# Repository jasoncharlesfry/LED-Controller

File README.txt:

This is a three channel analog LED dimmer. It operates at 15-60V and 1A per channel. It is based on the iw339 PWM controller IC. There is no current regulation so this board is only appropriate for LEDs with current-limiting resistors.

The pulse width of each channel is controlled by a 100k potentiometer. It is easier to control the brightness precisely with an audio taper pot. 

The board has positions for 4 switches. SW0 breaks VIN for all channels. SW1, SW2, and SW3 break VIN for channels 1, 2, and 3 respectively. All of the switches are optional and may be replaced with jumper wires depending on what is convenient for the application. 

The mosfet listed on the bom may not be in stock and can be replaced with any TO-252 mosfet with appropriate specifications (the threshold should be below 5V, Vgs-max should be above 15V, Vds-max should be above VIN, and Id-max should be above the current drawn by the LEDs).

Do not replace the fuse with a jumper. Use an appropriately sized 2AG fast-blow fuse.

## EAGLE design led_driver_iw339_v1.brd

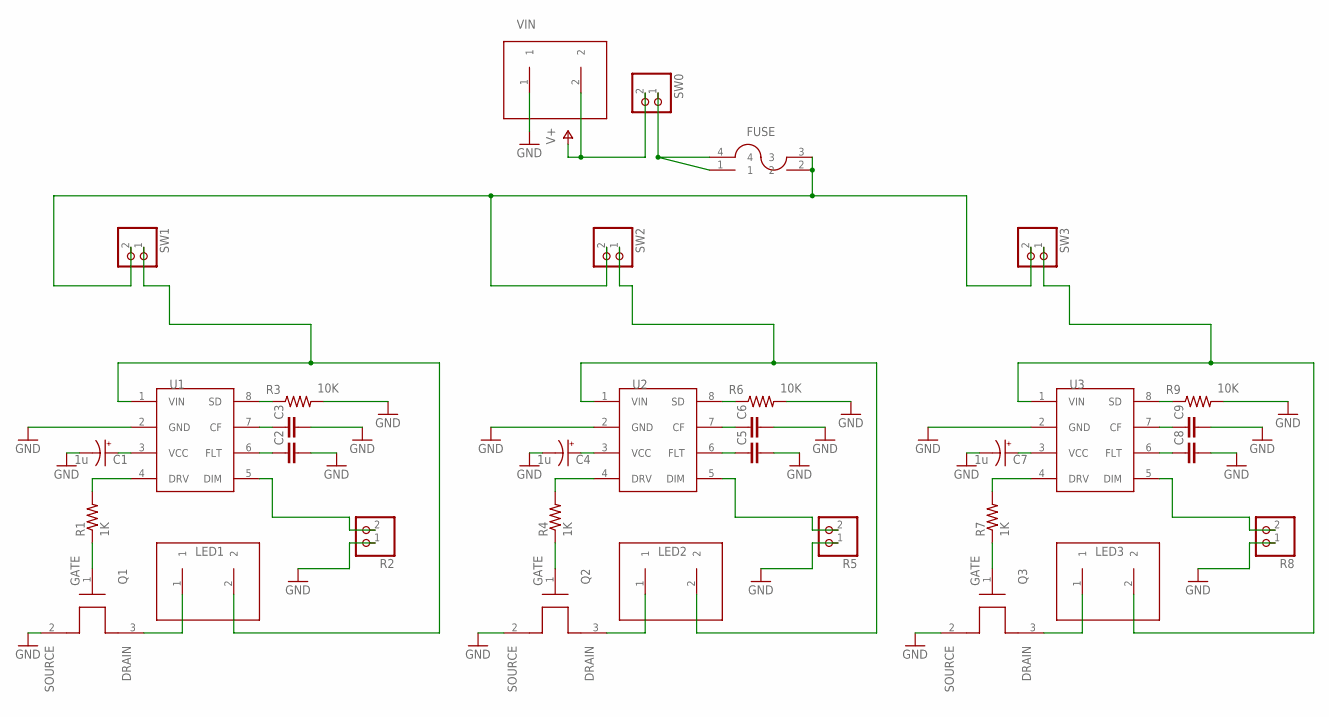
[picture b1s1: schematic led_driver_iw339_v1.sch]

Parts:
C1, C4, C7: 1u; E2-5
C2, C5, C8: 0.1u; C050-025X075
C3, C6, C9: 1n; C050-025X075
FUSE: 5X20_FUSE_HOLDER
LED1, LED2, LED3: TERMINAL_BLOCK
Q1, Q2, Q3: DMTH6016LK3; TO252
R1, R4, R7: 1K; 0207/10
R2, R5, R8: PINHD-1X2; 1X02
R3, R6, R9: 10K; 0207/10
SW0, SW1, SW2, SW3: PINHD-1X2; 1X02
U1, U2, U3: IW339"; SOIC-8
VIN: TERMINAL_BLOCK

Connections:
CF1: C3.1, U1.7 (CF)
CF2: C6.1, U2.7 (CF)
CF3: C9.1, U3.7 (CF)
DIM1: R2.2, U1.5 (DIM)
DIM2: R5.2, U2.5 (DIM)
DIM3: R8.2, U3.5 (DIM)
DRAIN1: LED1.1, Q1.3 (DRAIN)
DRAIN2: LED2.1, Q2.3 (DRAIN)
DRAIN3: LED3.1, Q3.3 (DRAIN)
DRV1: R1.2, U1.4 (DRV)
DRV2: R4.2, U2.4 (DRV)
DRV3: R7.2, U3.4 (DRV)
FLT1: C2.1, U1.6 (FLT)
FLT2: C5.1, U2.6 (FLT)
FLT3: C8.1, U3.6 (FLT)
GATE1: Q1.1 (GATE), R1.1
GATE2: Q2.1 (GATE), R4.1
GATE3: Q3.1 (GATE), R7.1
GND: C1.-, C2.2, C3.2, C4.-, C5.2, C6.2, C7.-, C8.2, C9.2, Q1.2 (SOURCE), Q2.2 (SOURCE), Q3.2 (SOURCE), R2.1, R3.2, R5.1, R6.2, R8.1, R9.2, U1.2 (GND), U2.2 (GND), U3.2 (GND), VIN.1
SD1: R3.1, U1.8 (SD)
SD2: R6.1, U2.8 (SD)
SD3: R9.1, U3.8 (SD)
SW0OUT: FUSE.1, FUSE.4, SW0.1
VCC1: C1.+, U1.3 (VCC)
VCC2: C4.+, U2.3 (VCC)
VCC3: C7.+, U3.3 (VCC)
VIN: SW0.2, VIN.2
VIN0: FUSE.2, FUSE.3, SW1.2, SW2.2, SW3.2
VIN1: LED1.2, SW1.1, U1.1 (VIN)
VIN2: LED2.2, SW2.1, U2.1 (VIN)
VIN3: LED3.2, SW3.1, U3.1 (VIN)

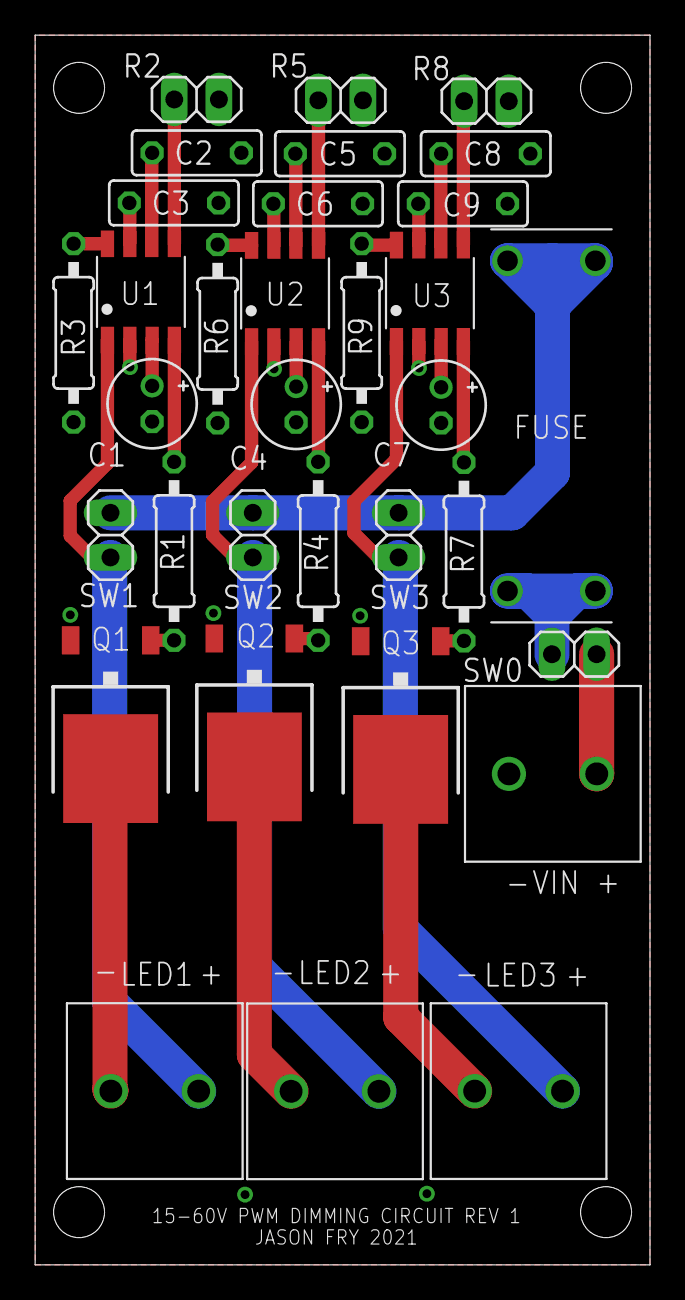
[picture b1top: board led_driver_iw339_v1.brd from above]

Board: 2 copper layers, 35.0 x 70.0 mm, 33 parts (0 on the bottom side), 31 nets.

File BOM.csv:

Schematic Name,Description,Mfg,Mfg #,cost/unit,quantity
"VIN, LED1, LED2, LED3",Terminal block,Phoenix Contact,1989447,0.41,4
"U1, U2, U3",PWM IC,Dialog Semiconductor,iw339-00,0.61,3
-,Enclosure,Hammond Manufacturing,RL6105BK,3.08,1
"SW0, SW1, SW2, SW3",Toggle Switch,E-Switch,100SP1T1B1M1QEH,2.32,4
"Q1, Q2, Q3",Mosfet,Diodes Incorporated,DMTH6016LK3-13,0.54,3
FUSE,Fuse Clip,Littelfuse,01110501Z ,0.14,2
"R2, R5, R8",100k Potentiometer,TT Electronics,P160KNP-0FC18B100K ,1.03,3
"C1, C4, C7",1uF Capacitor,,,,3
"C2, C5, C8",0.1uF Capacitor,,,,3
"C3, C6, C9",1nF Capacitor,,,,3
"R1, R4, R7",1k Resistor,,,,3
"R3, R6, R9",10k Resistor,,,,3

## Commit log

2021-09-29 added schematic and board
2021-09-29 added README and BOM
